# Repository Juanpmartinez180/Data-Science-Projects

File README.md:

# Data-Science-Projects
Personal Data science projects. 

Kaggle_competition folder -> Notebooks and scripts with the necesary datasets to run them. All related to Kaggle data science competitions and challenges

Tensorflow folder -> Notebooks using Tensorflow python library to solve Machine learning and Deep learning problems.

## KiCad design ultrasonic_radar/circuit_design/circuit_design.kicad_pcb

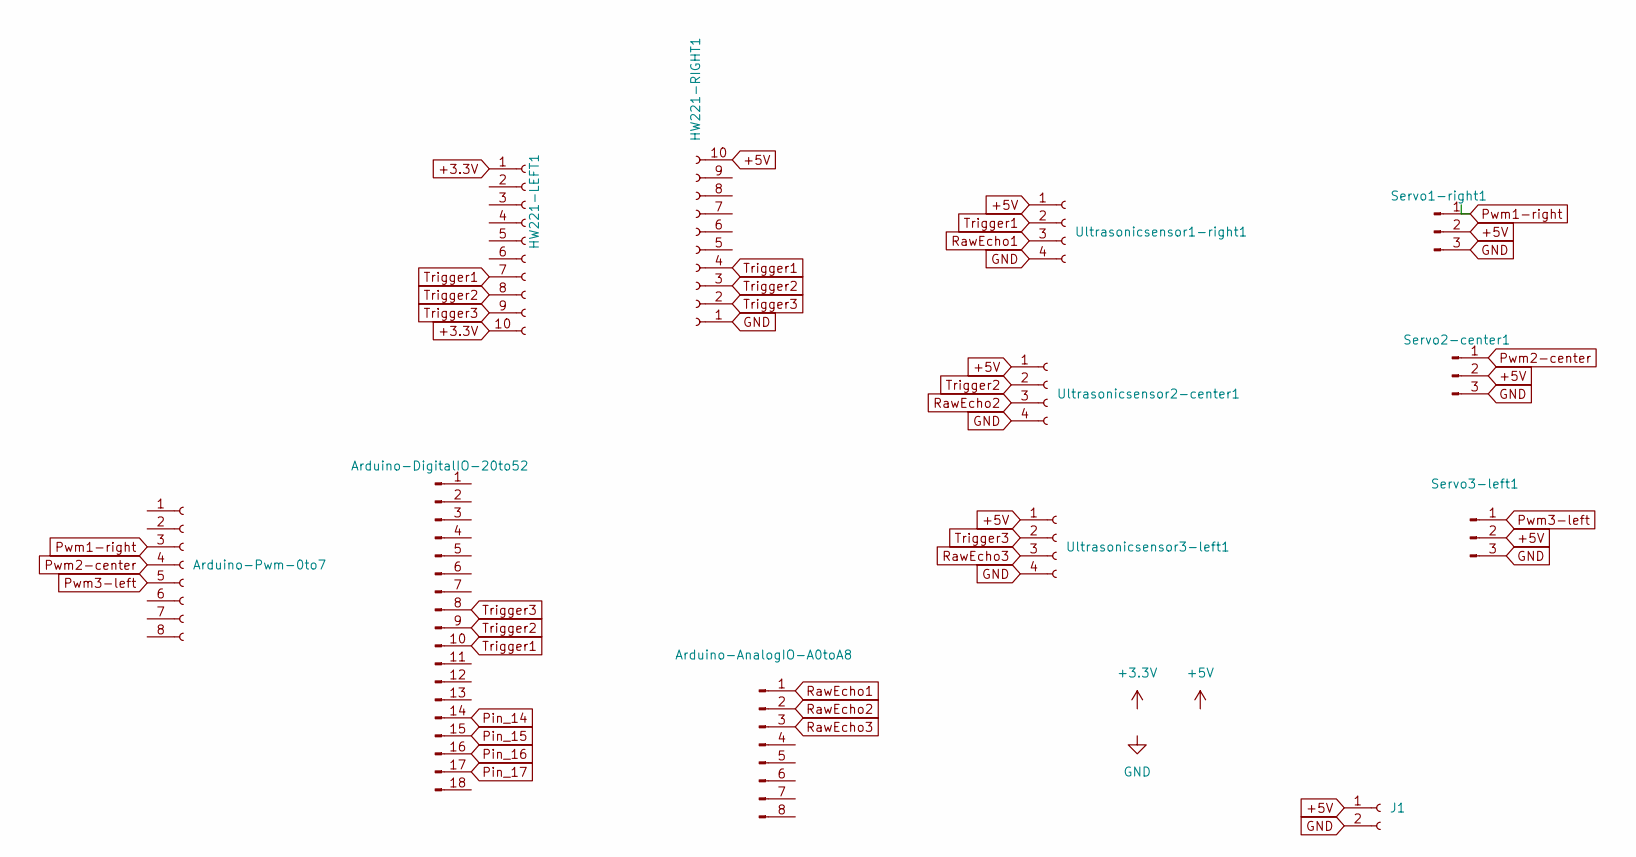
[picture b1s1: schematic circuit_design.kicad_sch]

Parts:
Arduino-AnalogIO-A0toA8: Conn_01x08_Pin; PinHeader_1x08_P2.54mm_Vertical
Arduino-DigitalIO-20to52: Conn_01x18_Pin; PinHeader_1x18_P2.54mm_Vertical
Arduino-Pwm-0to7: Conn_01x08_Socket; PinHeader_1x08_P2.54mm_Vertical
HW221-LEFT1, HW221-RIGHT1: Conn_01x10_Socket; PinSocket_1x10_P2.54mm_Vertical
J1: Conn_01x02_Socket; Molex_KK-396_5273-02A_1x02_P3.96mm_Vertical
Servo1-right1, Servo2-center1, Servo3-left1: Conn_01x03_Pin; PinSocket_1x03_P2.54mm_Vertical
Ultrasonicsensor1-right1, Ultrasonicsensor2-center1, Ultrasonicsensor3-left1: Conn_01x04_Socket; PinSocket_1x04_P2.54mm_Vertical

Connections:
+3.3V: HW221-LEFT1.1, HW221-LEFT1.10
+5V: HW221-RIGHT1.10, J1.1, Servo1-right1.2, Servo2-center1.2, Servo3-left1.2, Ultrasonicsensor1-right1.1, Ultrasonicsensor2-center1.1, Ultrasonicsensor3-left1.1
GND: HW221-RIGHT1.1, J1.2, Servo1-right1.3, Servo2-center1.3, Servo3-left1.3, Ultrasonicsensor1-right1.4, Ultrasonicsensor2-center1.4, Ultrasonicsensor3-left1.4
Pin_14: Arduino-DigitalIO-20to52.14
Pin_15: Arduino-DigitalIO-20to52.15
Pin_16: Arduino-DigitalIO-20to52.16
Pin_17: Arduino-DigitalIO-20to52.17
Pwm1-right: Arduino-Pwm-0to7.3, Servo1-right1.1
Pwm2-center: Arduino-Pwm-0to7.4, Servo2-center1.1
Pwm3-left: Arduino-Pwm-0to7.5, Servo3-left1.1
RawEcho1: Arduino-AnalogIO-A0toA8.1, Ultrasonicsensor1-right1.3
RawEcho2: Arduino-AnalogIO-A0toA8.2, Ultrasonicsensor2-center1.3
RawEcho3: Arduino-AnalogIO-A0toA8.3, Ultrasonicsensor3-left1.3
Trigger1: Arduino-DigitalIO-20to52.10, HW221-LEFT1.7, HW221-RIGHT1.4, Ultrasonicsensor1-right1.2
Trigger2: Arduino-DigitalIO-20to52.9, HW221-LEFT1.8, HW221-RIGHT1.3, Ultrasonicsensor2-center1.2
Trigger3: Arduino-DigitalIO-20to52.8, HW221-LEFT1.9, HW221-RIGHT1.2, Ultrasonicsensor3-left1.2

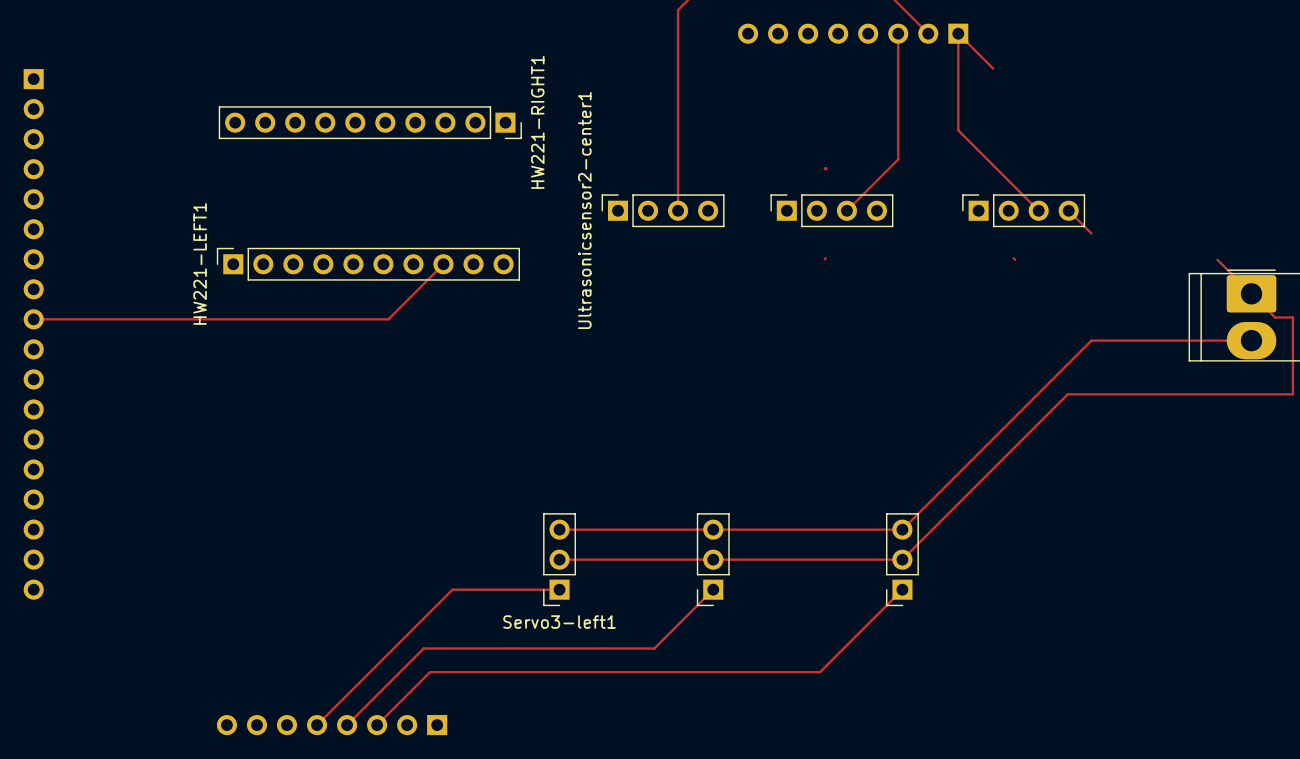
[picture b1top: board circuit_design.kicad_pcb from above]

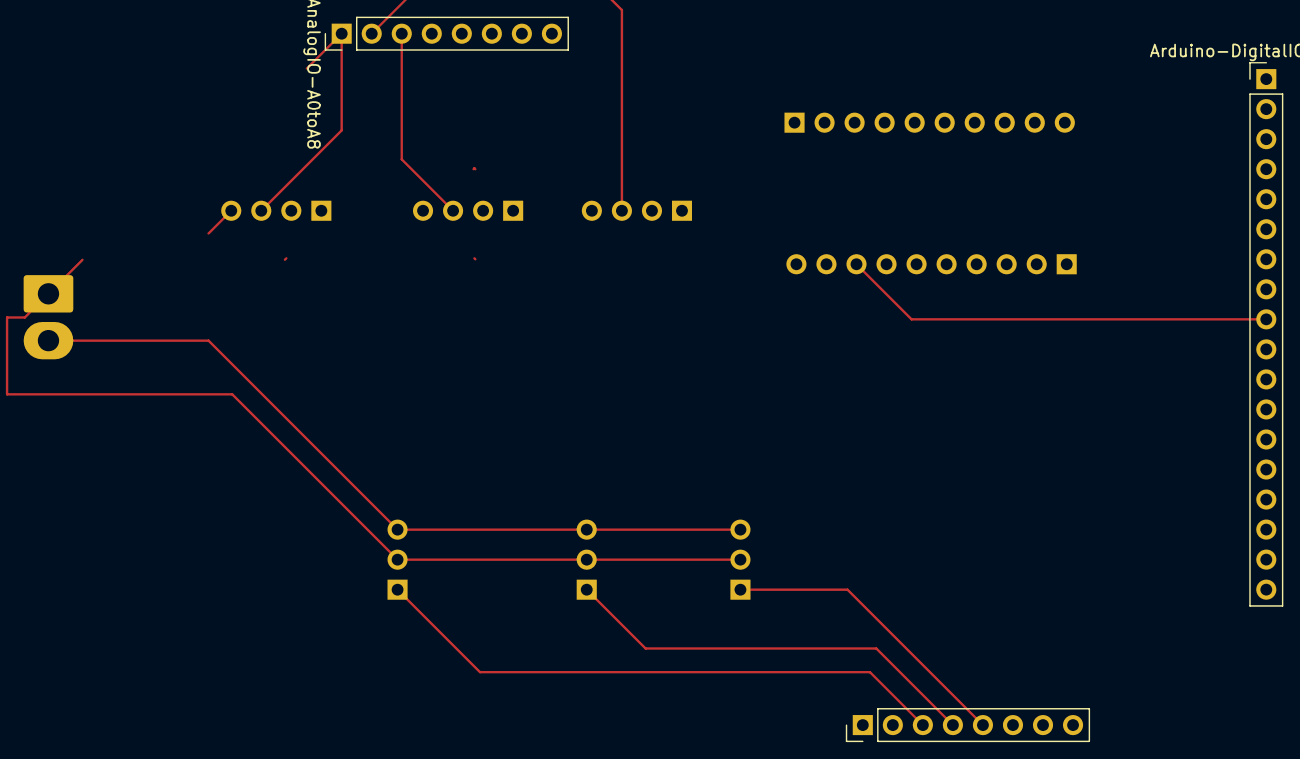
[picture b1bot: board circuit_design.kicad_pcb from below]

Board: 2 copper layers, 12 parts (3 on the bottom side), 12 nets.

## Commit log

2021-05-10 Adding existing scripts from my local repository
2021-05-10 Readme update
2021-05-15 Titanic challenge notebook upload
2022-02-05 dev: data generation almost complete
2022-02-05 dev: hand detection script
2022-02-16 datasets and scripts for ultrasonic radar project
2022-02-16 tensorflow cardiac anomaly detection scripts
2022-02-16 gitignore updated
2022-02-16 readme updated
2022-02-16 gitignore updated, no longer datasets persists
2022-02-16 titanic challenge sumittions added
2022-02-16 titanic challenge notebook added
2022-09-15 model training file update
2022-09-15 code to capture and analize data from arduino
2022-09-15 test label csv deleted
2022-09-21 captured data
2022-09-21 data processing file updated
2022-09-21 data read and plot script updated
2022-09-21 files moved and deleted
2022-09-22 helpers file with usefull functions to run data processing tasks
2022-09-22 notebook to run a capture and identify data pipeline
2022-09-22 captured data files updated
2022-09-22 gitignore updated with new directories
2022-09-22 data processing notebook heavily updated
2022-09-22 notebook to read the data from serial port heavily updated. Now is possible to read data from multiple sensors
2025-09-18 updating code 2025
2025-09-18 adding arduino files
2025-09-22 folder rename, files relocated
2025-09-22 new folder for the arduino board scripts
2025-09-22 captured data from testing
2025-09-22 models relocated for the new automated python script
2025-09-22 automated script to see realtime predictions
2025-09-22 updated scripts to make it more clear and effective
2025-09-22 new notebook with the functionalities deleted from the main notebook scripts
2025-09-22 no changes.
2025-09-22 new approach to find the peaks in the signal
2025-09-24 revised arduino c++ code for multiple and 1 sensor configurations
2025-09-24 new ai-revised c++ code for multisensor radar
2025-09-24 serial comm updated. more reliable and faster
2025-09-24 updated serial read logic, more liable
2025-09-24 document reference for sensor connection
2025-09-25 cleaning unused or deprecated code
2025-09-25 new captured data logs
2025-09-25 new function using signal peak detection library implemented in the code and notebook
2025-09-25 updated serial read and ohters
2025-09-25 arduino C code relocated
2025-09-25 document image
2025-10-10 cleaning script
2025-10-10 analysis for the step and rotation strategy
2025-10-10 new approach to generate synthetic dataset
2025-10-10 sonar ui now uses binary serial communication
2025-10-10 keeping serial comm sonar ui script as archive
2025-10-10 arduino C code for sonar using binary comm
2025-10-10 update gitignore, delete unneded file
2025-10-10 test for the sg90 arduino servo
2025-10-17 saving old files and moving to a legacy code folder
2025-10-17 deleting files and updating gitignore
2025-10-17 script to generate synthetic dataset
2025-10-17 new ML model training
2025-10-17 new step by step synthetic data generation analyis
2025-11-16 updating gitignore
2025-11-16 Guardado del dataset directo sobre el archivo para optimizar performance al guardado
2025-11-16 reoptimizando la grilla del area visible de los sensores y la escena
2025-11-17 area de la escena optimizada, solo los cuadarntes cubiertos por los sensores
2025-11-17 guardado del dataset como archivo binario, optimizacion de funciones
2025-11-17 mapa de cuadrantes para reconstruir las labels a posiciones x, y
2025-11-17 imagen de antes y despues del pruning de cuadrantes
2025-11-17 reconstruccion y visualizacion de los labels al espacio bidimensional
2025-11-17 ajuste del modelo de ml. nuevo modelo de ML entrenado. en proceso de testing
2025-11-17 nueva simulacion en tiempo real para visualizar las labels vs predicciones versus el threshold de deteccion
2025-11-17 nuevo notebooks para testing y evaluacion del modelo de ml usando datos sinteticos
2025-11-17 removing datasets from gitignore
2025-11-17 archivos de mapeo y features validados al 17-11-25
2025-11-18 deleting old datasets
2025-11-18 desarrollo de metricas custom para evaluacion de performance del modelo de ML. Analisis de montecarlo
2025-11-18 incluir metricas custom para el visualizador de predicciones, con un parametro de radio de inclusion.
2025-11-18 test de servos para arduino. gitignore incluye checkpoints
2025-11-18 guardado de parametros de normalizacion del dataset. necesarios para la inferencia
2025-11-18 nuevo UI para el sonar acorde a los ultimos cambios del approach. Modificacion a la funcion de deteccion de picos para mayor precision
2025-11-18 archivos de coordenadas y stats de normalizacion
2025-11-19 new script to extract the base noise and calibrate the sensors. values saved to a file that is used for the Sonar script. gitignore updated
2025-11-19 new approach to use a dynamic threshold based on the base noise captured during the system calibration. Sliders included to calibrate each sensor peak detection sentitivity
2025-11-19 development of the dynamic thresholds, and testing using captured data
2025-11-19 kicad project for circuit and pcb design
2025-11-20 add kicad temp files to gitignore
2025-11-20 circuit pcb design updated
2025-11-20 check payload lenght during read
2025-11-21 deleting unneded files
